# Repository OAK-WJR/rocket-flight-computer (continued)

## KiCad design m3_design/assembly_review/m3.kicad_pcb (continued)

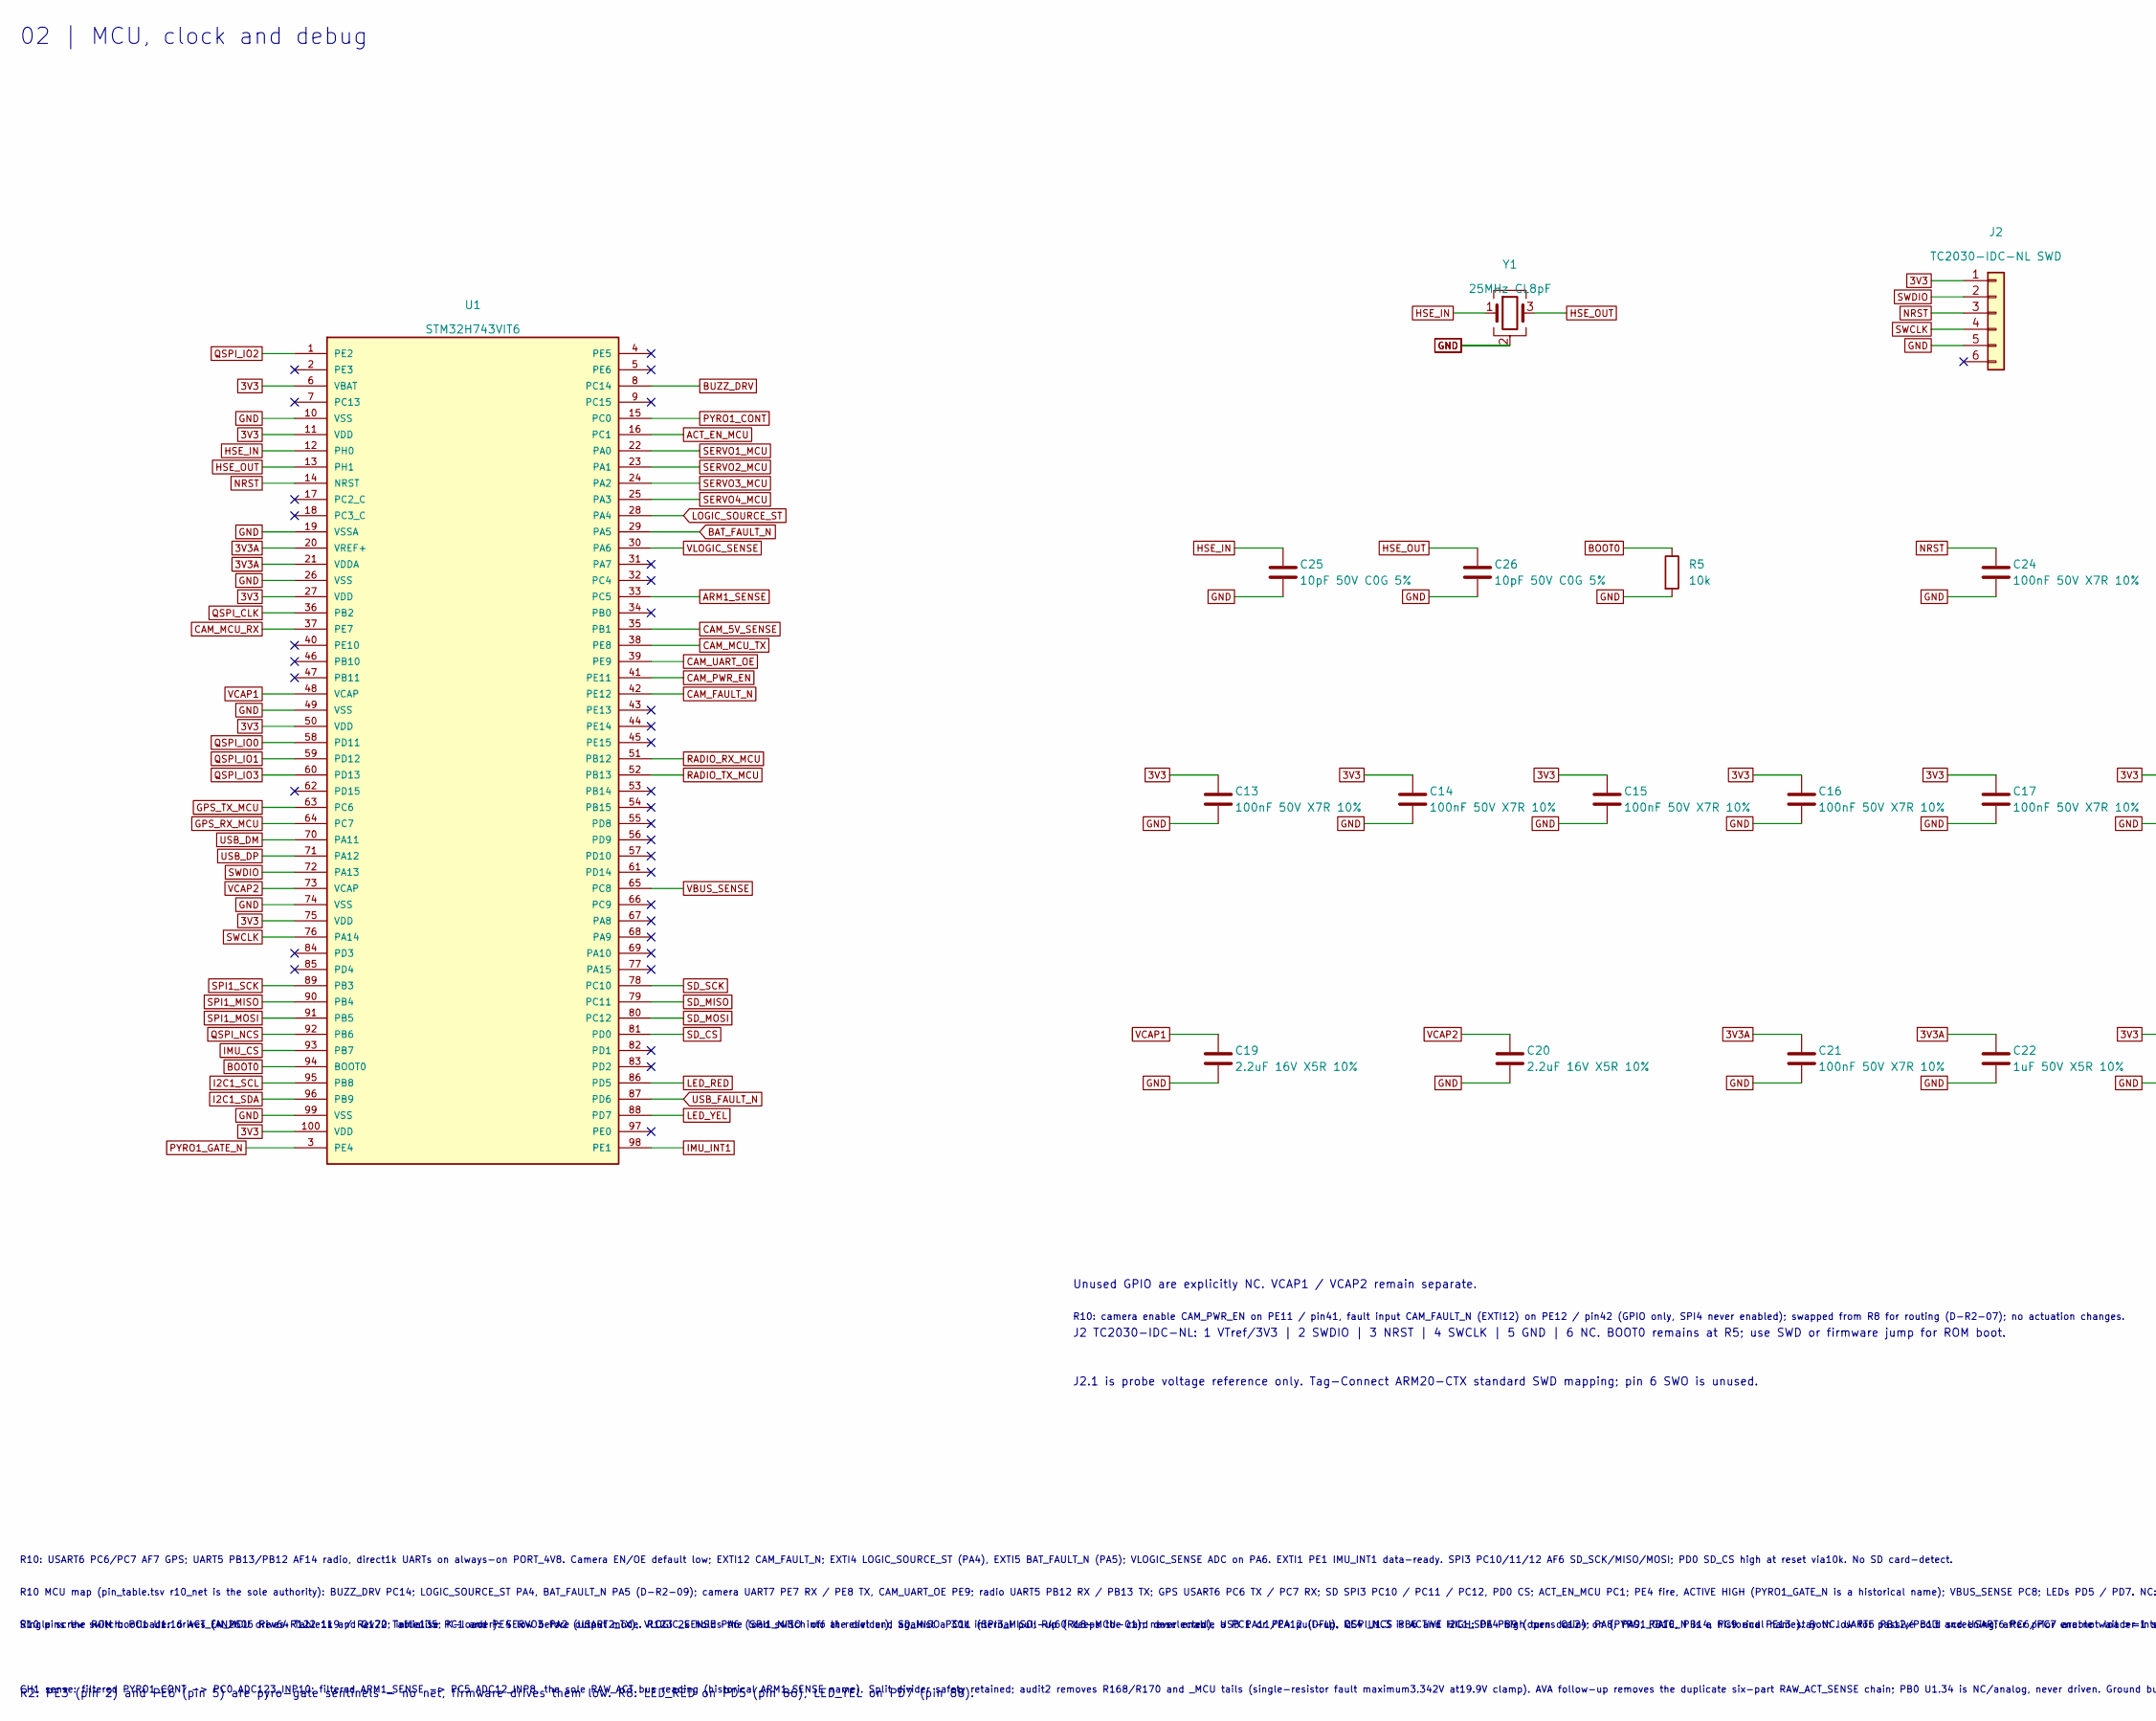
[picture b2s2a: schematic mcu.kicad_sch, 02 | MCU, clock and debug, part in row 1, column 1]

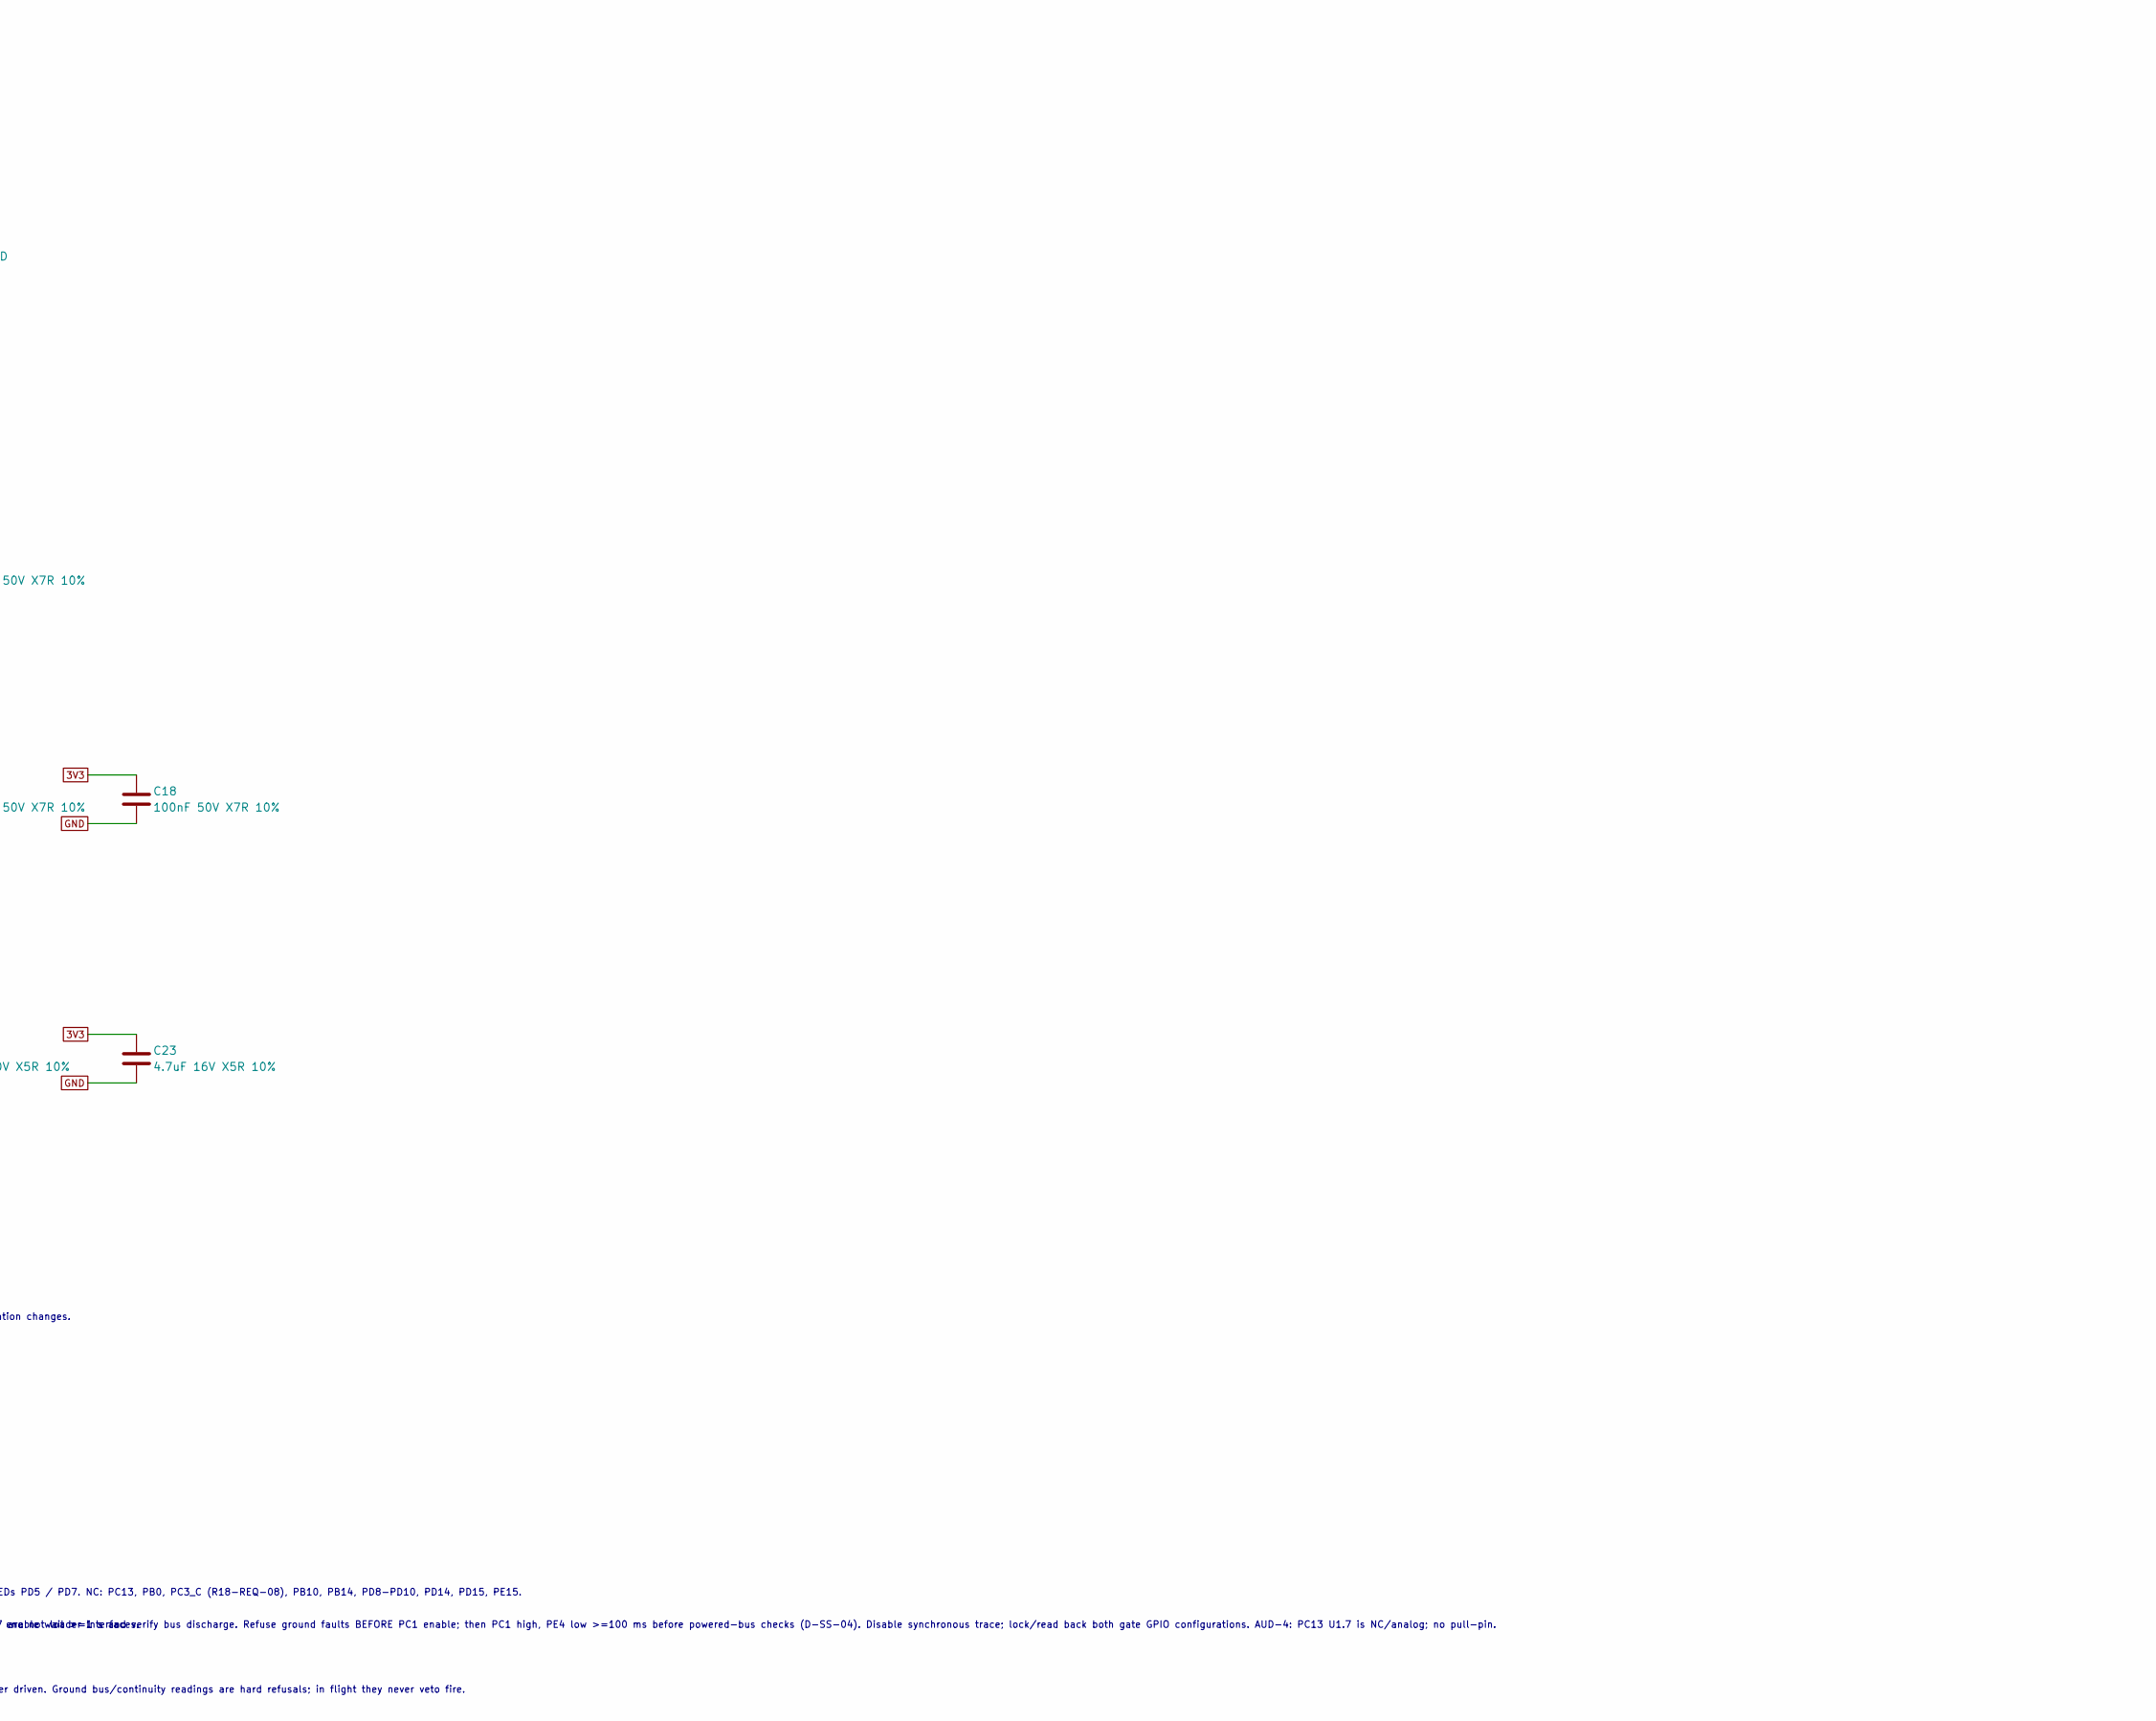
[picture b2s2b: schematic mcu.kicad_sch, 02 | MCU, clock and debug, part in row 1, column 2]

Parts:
C13, C14, C15, C16, C17, C18, C21, C24: 100nF 50V X7R 10%; C0402; Manufacturer Part CL05B104KB54PNC; LCSC C307331
C19, C20: 2.2uF 16V X5R 10%; C0603; Manufacturer Part CL10A225KO8NNNC; LCSC C23630
C22: 1uF 50V X5R 10%; C0603; Manufacturer Part CL10A105KB8NNNC; LCSC C15849
C23: 4.7uF 16V X5R 10%; C0603; Manufacturer Part CL10A475KO8NNNC; LCSC C19666
C25, C26: 10pF 50V C0G 5%; C0402; Manufacturer Part CL05C100JB5NNNC; LCSC C32949
J2: TC2030-IDC-NL SWD; M3_TC2030_IDC_NL; Manufacturer Part TC2030-IDC-NL
R5: 10k; R0402; Manufacturer Part 0402WGF1002TCE; LCSC C25744
U1: STM32H743VIT6; LQFP-100_L14.0-W14.0-P0.50-LS16.0-BL; Manufacturer Part STM32H743VIT6TR; LCSC C5271084
Y1: 25MHz CL8pF; CRYSTAL-SMD_4P-L3.2-W2.5-BL; Manufacturer Part NX3225GA-25.000M-STD-CRG-2; LCSC C1985619

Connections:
3V3: C13.1, C14.1, C15.1, C16.1, C17.1, C18.1, C23.1, J2.1, U1.6 (VBAT), U1.11 (VDD), U1.27 (VDD), U1.50 (VDD), U1.75 (VDD), U1.100 (VDD); also elsewhere on the board
3V3A: C21.1, C22.1, U1.20 (VREF+), U1.21 (VDDA); also elsewhere on the board
ACT_EN_MCU: U1.16 (PC1); also elsewhere on the board
ARM1_SENSE: U1.33 (PC5); also elsewhere on the board
BAT_FAULT_N: U1.29 (PA5); also elsewhere on the board
BOOT0: R5.1, U1.94 (BOOT0)
BUZZ_DRV: U1.8 (PC14); also elsewhere on the board
CAM_5V_SENSE: U1.35 (PB1); also elsewhere on the board
CAM_FAULT_N: U1.42 (PE12); also elsewhere on the board
CAM_MCU_RX: U1.37 (PE7); also elsewhere on the board
CAM_MCU_TX: U1.38 (PE8); also elsewhere on the board
CAM_PWR_EN: U1.41 (PE11); also elsewhere on the board
CAM_UART_OE: U1.39 (PE9); also elsewhere on the board
GND: C13.2, C14.2, C15.2, C16.2, C17.2, C18.2, C19.2, C20.2, C21.2, C22.2, C23.2, C24.2, C25.2, C26.2, J2.5, R5.2, U1.10 (VSS), U1.19 (VSSA), U1.26 (VSS), U1.49 (VSS), U1.74 (VSS), U1.99 (VSS), Y1.2 (G), Y1.4 (G); also elsewhere on the board
GPS_RX_MCU: U1.56 (PD9); also elsewhere on the board
GPS_TX_MCU: U1.55 (PD8); also elsewhere on the board
HSE_IN: C25.1, U1.12 (PH0), Y1.1
HSE_OUT: C26.1, U1.13 (PH1), Y1.3
I2C1_SCL: U1.95 (PB8); also elsewhere on the board
I2C1_SDA: U1.96 (PB9); also elsewhere on the board
IMU_CS: U1.93 (PB7); also elsewhere on the board
IMU_INT1: U1.98 (PE1); also elsewhere on the board
LED_RED: U1.86 (PD5); also elsewhere on the board
LED_YEL: U1.88 (PD7); also elsewhere on the board
LOGIC_SOURCE_ST: U1.28 (PA4); also elsewhere on the board
NRST: C24.1, J2.3, U1.14 (NRST)
PYRO1_CONT: U1.15 (PC0); also elsewhere on the board
PYRO1_GATE_N: U1.3 (PE4); also elsewhere on the board
QSPI_CLK: U1.36 (PB2); also elsewhere on the board
QSPI_IO0: U1.58 (PD11); also elsewhere on the board
QSPI_IO1: U1.59 (PD12); also elsewhere on the board
QSPI_IO2: U1.1 (PE2); also elsewhere on the board
QSPI_IO3: U1.60 (PD13); also elsewhere on the board
QSPI_NCS: U1.92 (PB6); also elsewhere on the board
RADIO_RX_MCU: U1.51 (PB12); also elsewhere on the board
RADIO_TX_MCU: U1.52 (PB13); also elsewhere on the board
SD_CS: U1.81 (PD0); also elsewhere on the board
SD_MISO: U1.79 (PC11); also elsewhere on the board
SD_MOSI: U1.80 (PC12); also elsewhere on the board
SD_SCK: U1.78 (PC10); also elsewhere on the board
SERVO1_MCU: U1.22 (PA0); also elsewhere on the board
SERVO2_MCU: U1.23 (PA1); also elsewhere on the board
SERVO3_MCU: U1.24 (PA2); also elsewhere on the board
SERVO4_MCU: U1.25 (PA3); also elsewhere on the board
SPI1_MISO: U1.90 (PB4); also elsewhere on the board
SPI1_MOSI: U1.91 (PB5); also elsewhere on the board
SPI1_SCK: U1.89 (PB3); also elsewhere on the board
SWCLK: J2.4, U1.76 (PA14)
SWDIO: J2.2, U1.72 (PA13)
USB_DM: U1.70 (PA11); also elsewhere on the board
USB_DP: U1.71 (PA12); also elsewhere on the board
USB_FAULT_N: U1.87 (PD6); also elsewhere on the board
VBUS_SENSE: U1.65 (PC8); also elsewhere on the board
VCAP1: C19.1, U1.48 (VCAP)
VCAP2: C20.1, U1.73 (VCAP)
VLOGIC_SENSE: U1.30 (PA6); also elsewhere on the board

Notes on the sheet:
02 | MCU, clock and debug
Unused GPIO are explicitly NC. VCAP1 / VCAP2 remain separate.
J2 TC2030-IDC-NL: 1 VTref/3V3 | 2 SWDIO | 3 NRST | 4 SWCLK | 5 GND | 6 NC. BOOT0 remains at R5; use SWD or firmware jump for ROM boot.
J2.1 is probe voltage reference only. Tag-Connect ARM20-CTX standard SWD mapping; pin 6 SWO is unused.
R2: PE3 (pin 2) and PE6 (pin 5) are pyro-gate sentinels - no net, firmware drives them low. R8: LED_RED on PD5 (pin 86), LED_YEL on PD7 (pin 88).
R10: USART6 PC6/PC7 AF7 GPS; UART5 PB13/PB12 AF14 radio, direct1k UARTs on always-on PORT_4V8. Camera EN/OE default low; EXTI12 CAM_FAULT_N; EXTI4 LOGIC_SOURCE_ST (PA4), EXTI5 BAT_FAULT_N (PA5); VLOGIC_SENSE ADC on PA6. EXTI1 PE1 IMU_INT1 data-ready. SPI3 PC10/11/12 AF6 SD_SCK/MISO/MOSI; PD0 SD_CS 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
Single screw switch: PC1 U1.16 ACT_EN_MCU drives R122 1k and Q122; initialise PC1 and PE4 low before output mode. R123 2k holds the load switch off at reset and against a 30k internal pull-up (R18-MCU-01); never enable a PC1 or PE4 pull-up. PE4 U1.3 is ACTIVE HIGH: PE4 high turns Q124 on (PYRO1_GAT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
R10: camera enable CAM_PWR_EN on PE11 / pin41, fault input CAM_FAULT_N (EXTI12) on PE12 / pin42 (GPIO only, SPI4 never enabled); swapped from R8 for routing (D-R2-07); no actuation changes.
R10 MCU map (pin_table.tsv r10_net is the sole authority): BUZZ_DRV PC14; LOGIC_SOURCE_ST PA4, BAT_FAULT_N PA5 (D-R2-09); camera UART7 PE7 RX / PE8 TX, CAM_UART_OE PE9; radio UART5 PB12 RX / PB13 TX; GPS USART6 PC6 TX / PC7 RX; SD SPI3 PC10 / PC11 / PC12, PD0 CS; ACT_EN_MCU PC1; PE4 fire, ACTIVE HI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
R10 pins the ROM bootloader drives (AN2606 Rev64 Table119 / Rev70 Table135; K-loader): SERVO3 PA2 (USART2_TX), VLOGIC_SENSE PA6 (SPI1_MISO into the divider), SD_MISO PC11 (SPI3_MISO; R460 keeps the card deselected), USB PA11/PA12 (DFU), QSPI_NCS PB6 and I2C1_SDA PB9 (open drain); PA8, PA9, PB10, PB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
CH1 sense: filtered PYRO1_CONT -> PC0 ADC123_INP10; filtered ARM1_SENSE -> PC5 ADC12_INP8, the sole RAW_ACT bus reading (historical ARM1_SENSE name). Split divider safety retained; audit2 removes R168/R170 and _MCU tails (single-resistor fault maximum3.342V at19.9V clamp). AVA follow-up removes the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

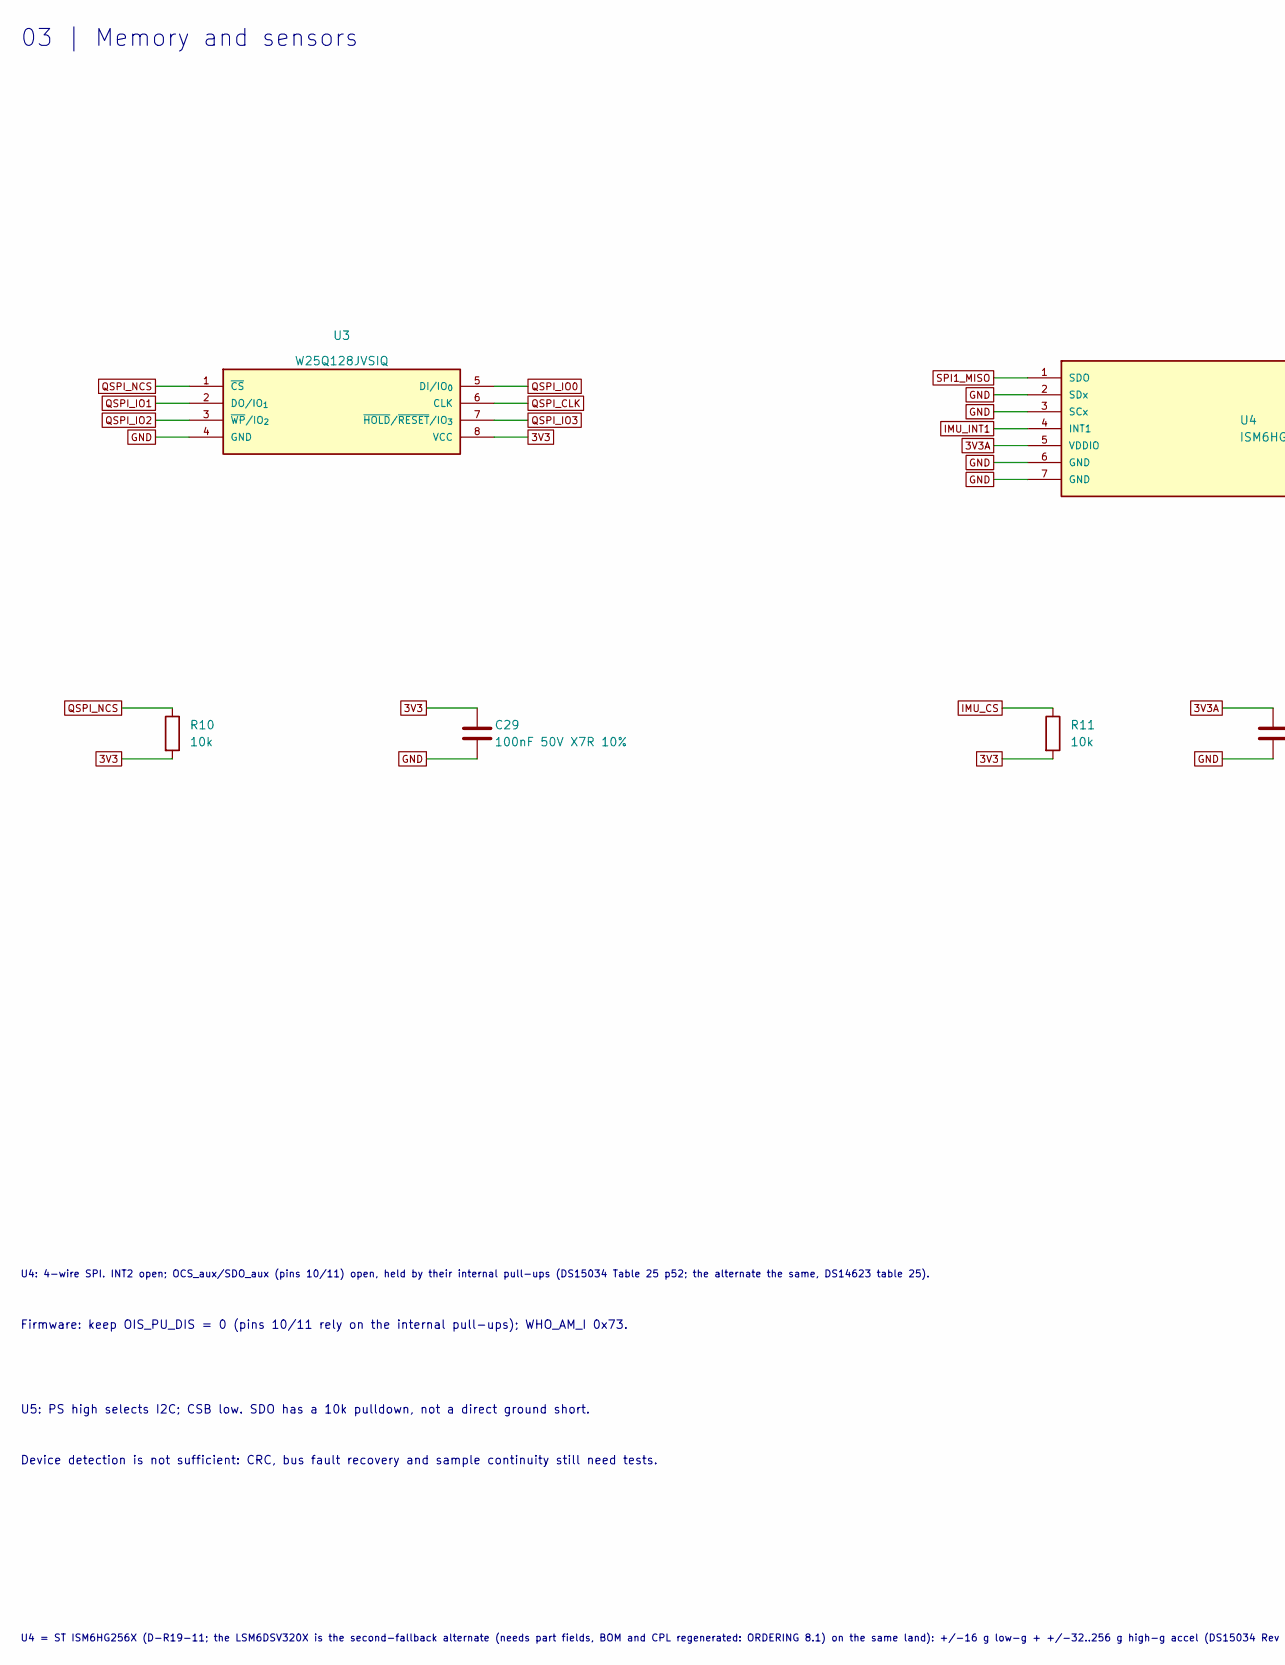
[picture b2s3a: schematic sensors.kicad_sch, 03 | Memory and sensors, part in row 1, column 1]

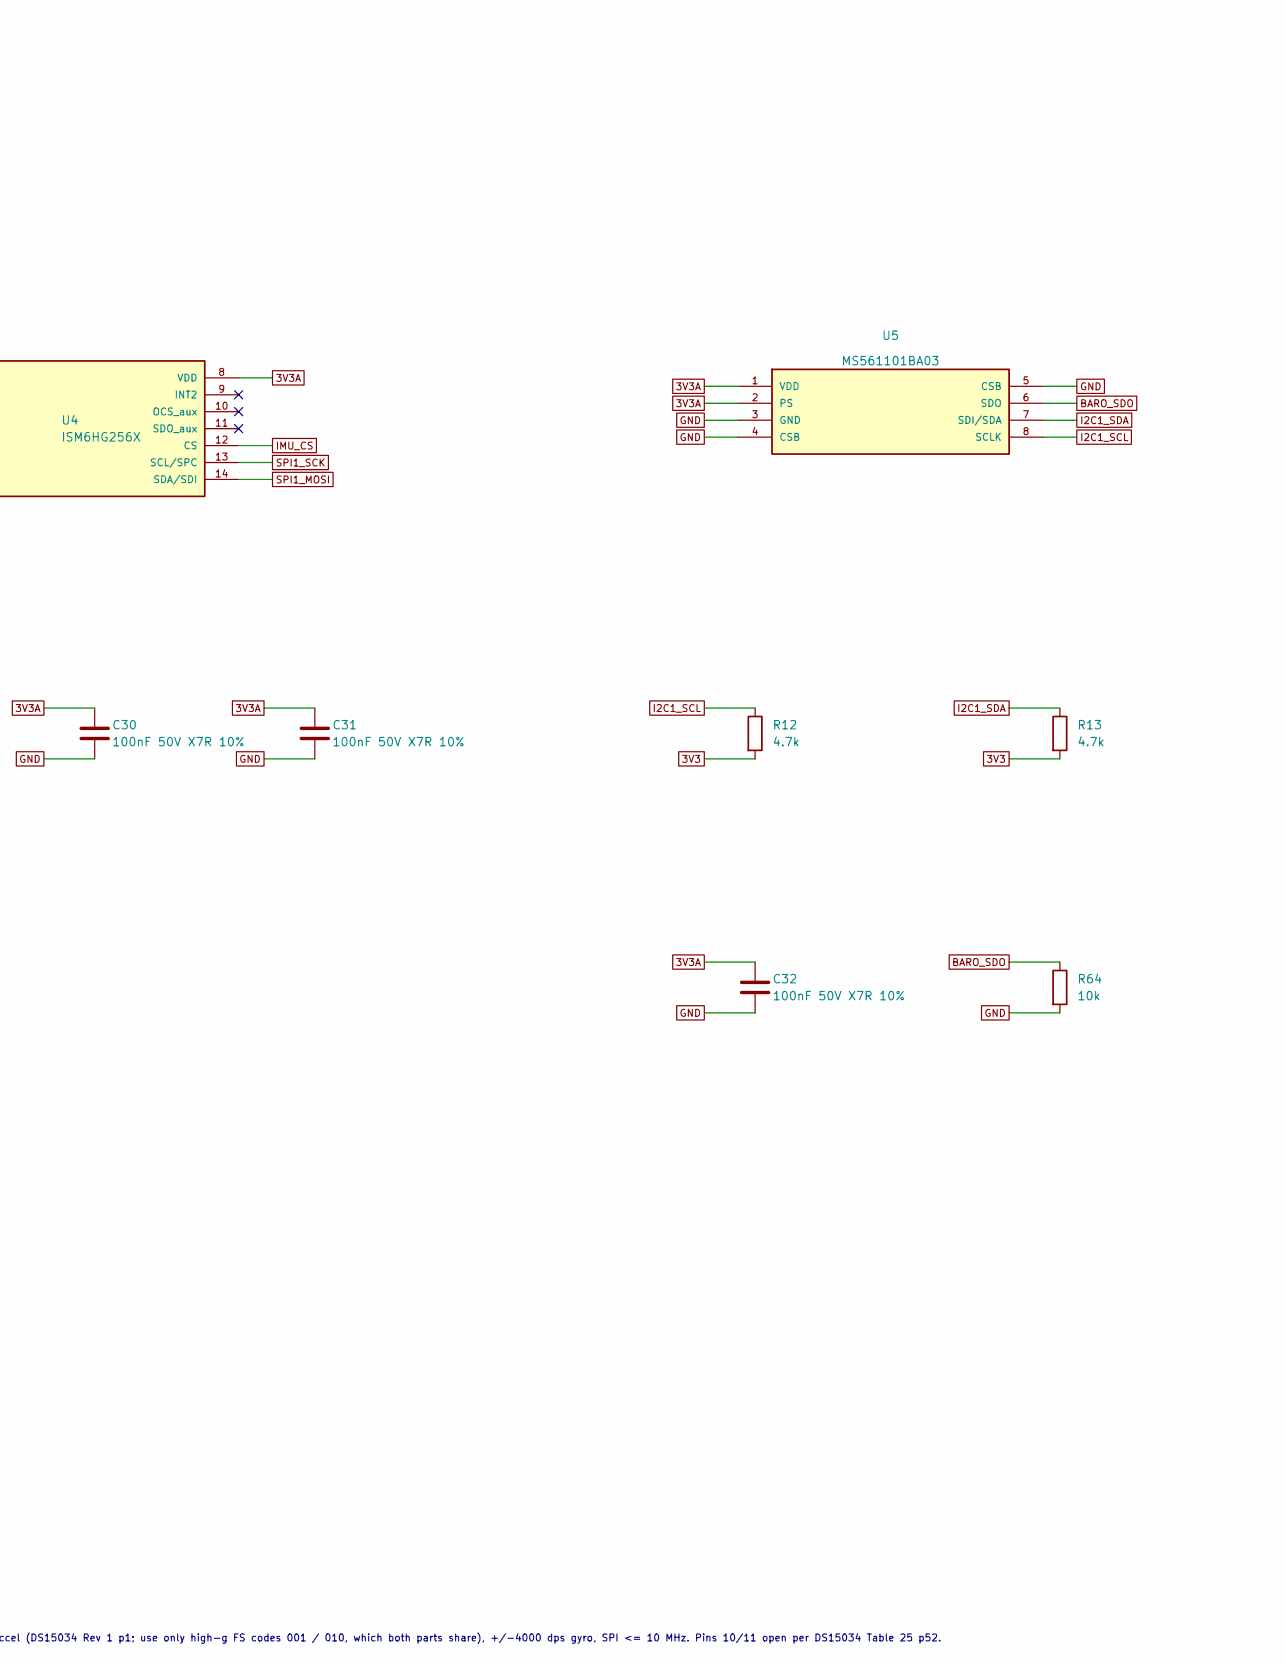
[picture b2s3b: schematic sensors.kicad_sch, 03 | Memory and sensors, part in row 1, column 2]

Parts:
C29, C30, C31, C32: 100nF 50V X7R 10%; C0402; Manufacturer Part CL05B104KB54PNC; LCSC C307331
R10, R11, R64: 10k; R0402; Manufacturer Part 0402WGF1002TCE; LCSC C25744
R12, R13: 4.7k; R0402; Manufacturer Part 0402WGF4701TCE; LCSC C25900
U3: W25Q128JVSIQ; SOIC-8_L5.3-W5.3-P1.27-LS8.0-BL; Manufacturer Part W25Q128JVSIQ; LCSC C97521
U4: ISM6HG256X; LGA-14_L3.0-W2.5-P0.50-TL; Manufacturer Part ISM6HG256XTR; LCSC C51931514
U5: MS561101BA03; SENSORS-SMD_MS5611-01BA03; Manufacturer Part MS561101BA03-50; LCSC C15639

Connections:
3V3: C29.1, R10.2, R11.2, R12.2, R13.2, U3.8 (VCC); also elsewhere on the board
3V3A: C30.1, C31.1, C32.1, U4.5 (VDDIO), U4.8 (VDD), U5.1 (VDD), U5.2 (PS); also elsewhere on the board
BARO_SDO: R64.1, U5.6 (SDO)
GND: C29.2, C30.2, C31.2, C32.2, R64.2, U3.4 (GND), U4.2 (SDx), U4.3 (SCx), U4.6 (GND), U4.7 (GND), U5.3 (GND), U5.4 (CSB), U5.5 (CSB); also elsewhere on the board
I2C1_SCL: R12.1, U5.8 (SCLK); also elsewhere on the board
I2C1_SDA: R13.1, U5.7 (SDI/SDA); also elsewhere on the board
IMU_CS: R11.1, U4.12 (CS); also elsewhere on the board
IMU_INT1: U4.4 (INT1); also elsewhere on the board
QSPI_CLK: U3.6 (CLK); also elsewhere on the board
QSPI_IO0: U3.5 (DI/IO_{0}); also elsewhere on the board
QSPI_IO1: U3.2 (DO/IO_{1}); also elsewhere on the board
QSPI_IO2: U3.3 (~WP/IO_{2}); also elsewhere on the board
QSPI_IO3: U3.7 (~HOLD/~RESET/IO_{3}); also elsewhere on the board
QSPI_NCS: R10.1, U3.1 (~CS); also elsewhere on the board
SPI1_MISO: U4.1 (SDO); also elsewhere on the board
SPI1_MOSI: U4.14 (SDA/SDI); also elsewhere on the board
SPI1_SCK: U4.13 (SCL/SPC); also elsewhere on the board

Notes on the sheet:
03 | Memory and sensors
Firmware: keep OIS_PU_DIS = 0 (pins 10/11 rely on the internal pull-ups); WHO_AM_I 0x73.
U5: PS high selects I2C; CSB low. SDO has a 10k pulldown, not a direct ground short.
Device detection is not sufficient: CRC, bus fault recovery and sample continuity still need tests.
U4 = ST ISM6HG256X (D-R19-11; the LSM6DSV320X is the second-fallback alternate (needs part fields, BOM and CPL regenerated: ORDERING 8.1) on the same land): +/-16 g low-g + +/-32..256 g high-g accel (DS15034 Rev 1 p1; use only high-g FS codes 001 / 010, which both parts share), +/-4000 dps gyro, SP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
U4: 4-wire SPI. INT2 open; OCS_aux/SDO_aux (pins 10/11) open, held by their internal pull-ups (DS15034 Table 25 p52; the alternate the same, DS14623 table 25).

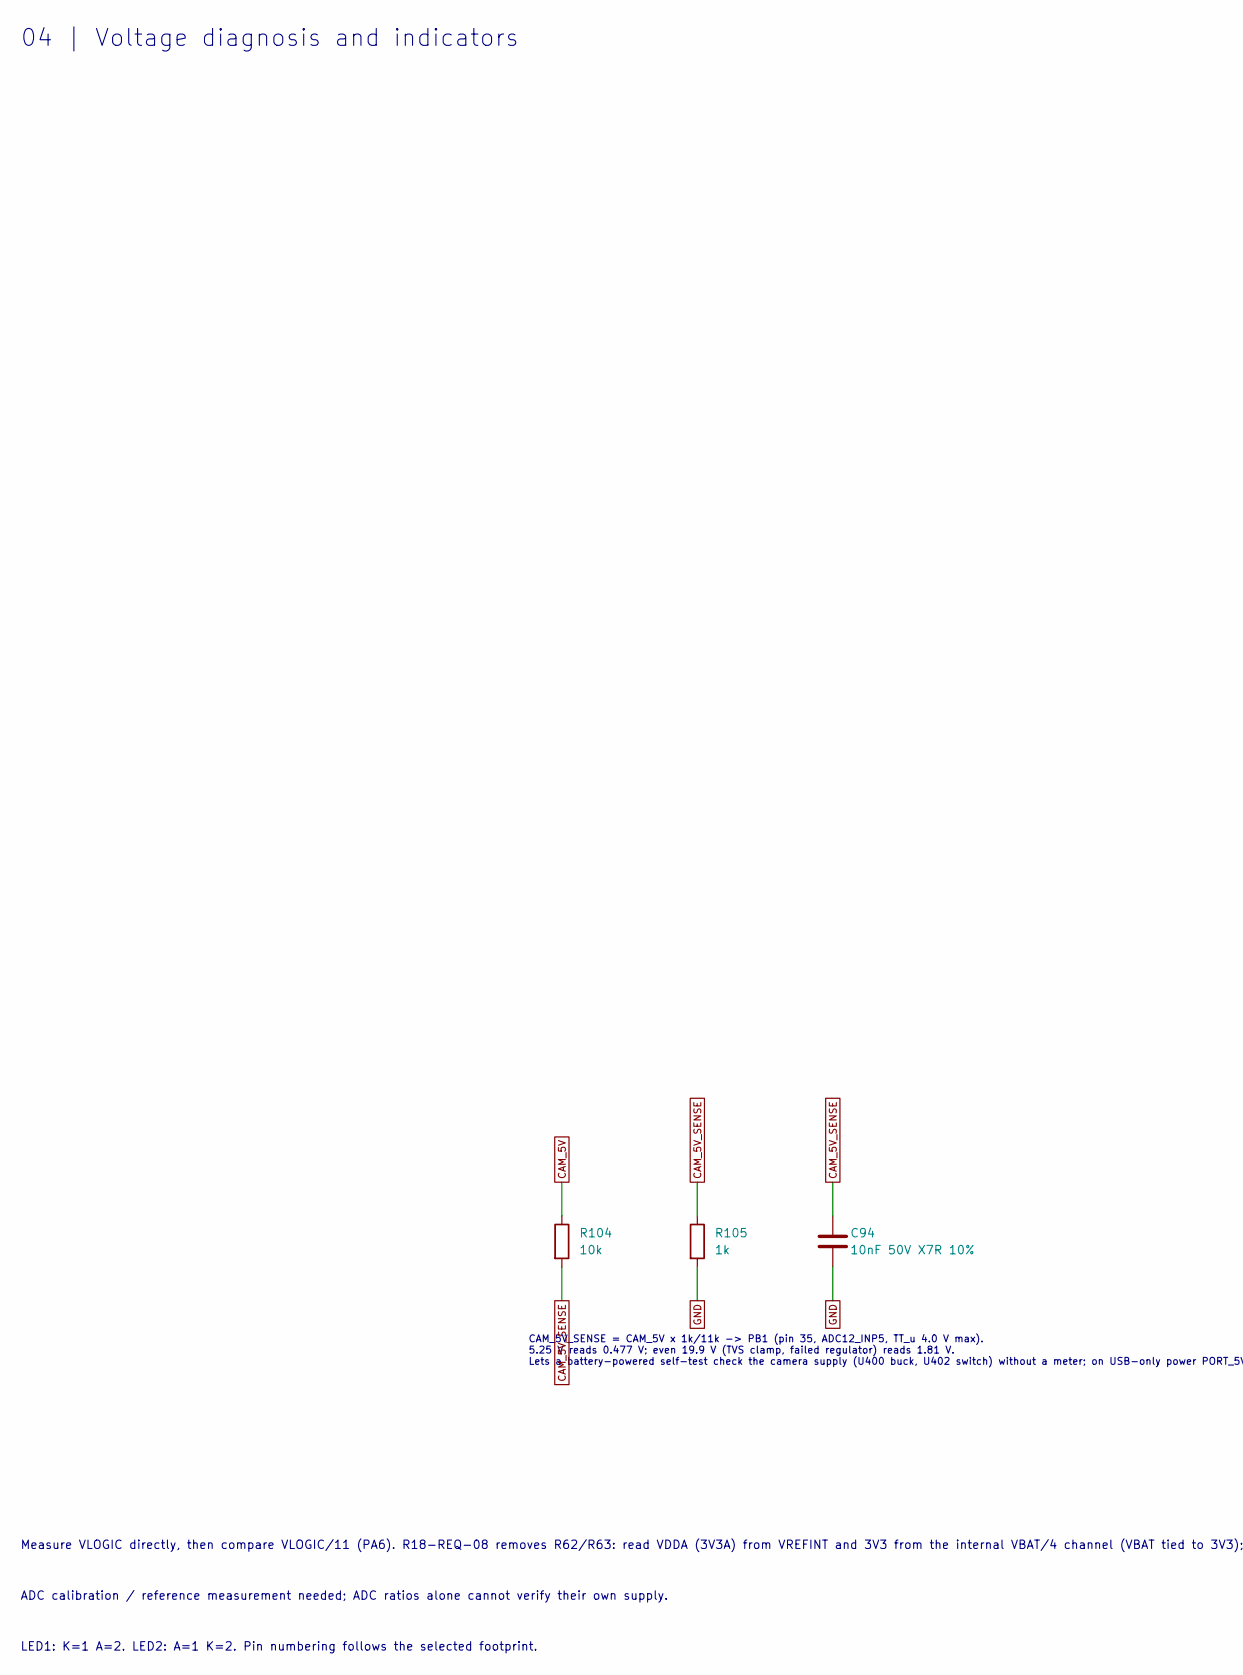
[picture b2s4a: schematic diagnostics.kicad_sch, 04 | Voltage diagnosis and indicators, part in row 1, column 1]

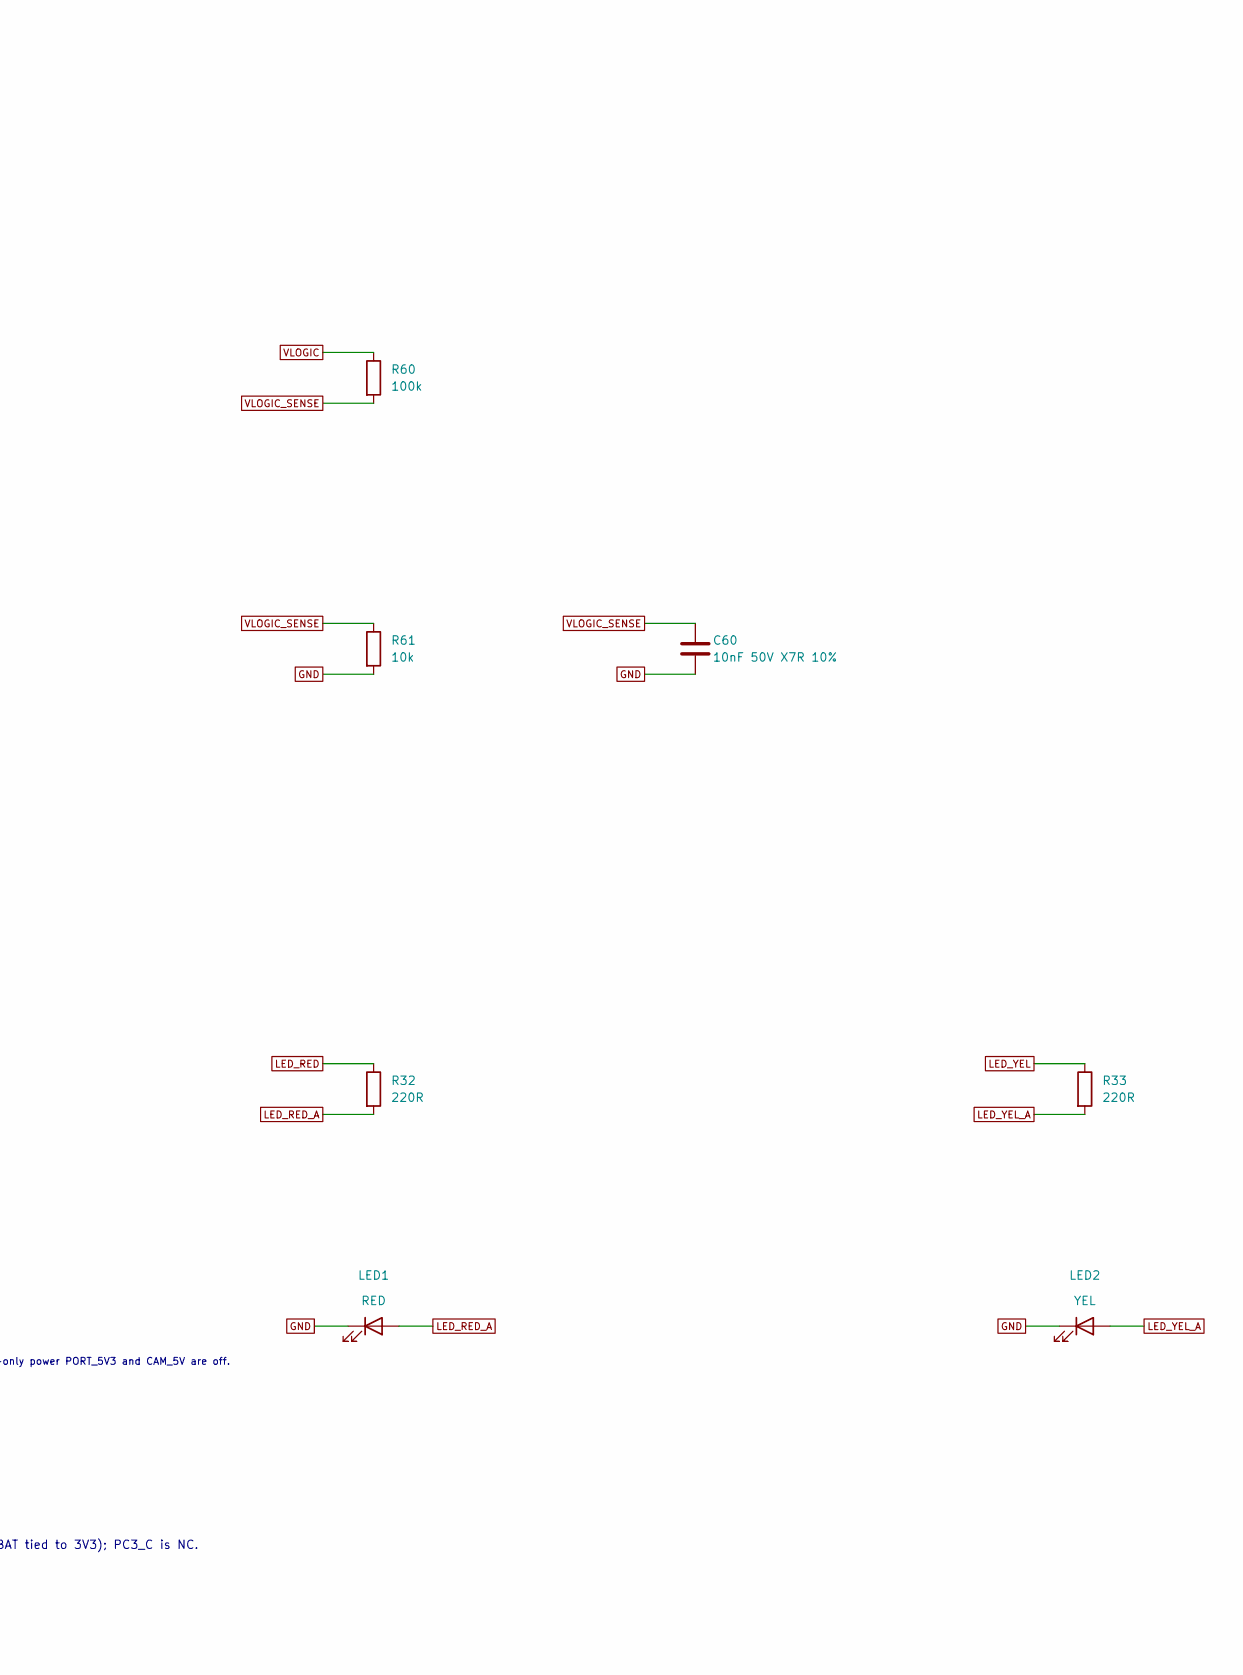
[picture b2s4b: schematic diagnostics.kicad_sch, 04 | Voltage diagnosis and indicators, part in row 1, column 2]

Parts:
C60, C94: 10nF 50V X7R 10%; C0603; Manufacturer Part 0603B103K500NT; LCSC C57112
LED1: RED; M3_NCD0805R1_K1; Manufacturer Part NCD0805R1; LCSC C84256
LED2: YEL; M3_KT0805Y_A1; Manufacturer Part KT-0805Y; LCSC C2296
R32, R33: 220R; R0805; Manufacturer Part 0805W8F2200T5E; LCSC C17557
R60: 100k; R0402; Manufacturer Part 0402WGF1003TCE; LCSC C25741
R61, R104: 10k; R0402; Manufacturer Part 0402WGF1002TCE; LCSC C25744
R105: 1k; R0402; Manufacturer Part 0402WGF1001TCE; LCSC C11702

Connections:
CAM_5V: R104.1; also elsewhere on the board
CAM_5V_SENSE: C94.1, R104.2, R105.1; also elsewhere on the board
GND: C60.2, C94.2, LED1.1 (K), LED2.2 (K), R61.2, R105.2; also elsewhere on the board
LED_RED: R32.1; also elsewhere on the board
LED_RED_A: LED1.2 (A), R32.2
LED_YEL: R33.1; also elsewhere on the board
LED_YEL_A: LED2.1 (A), R33.2
VLOGIC: R60.1; also elsewhere on the board
VLOGIC_SENSE: C60.1, R60.2, R61.1; also elsewhere on the board

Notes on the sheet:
04 | Voltage diagnosis and indicators
Measure VLOGIC directly, then compare VLOGIC/11 (PA6). R18-REQ-08 removes R62/R63: read VDDA (3V3A) from VREFINT and 3V3 from the internal VBAT/4 channel (VBAT tied to 3V3); PC3_C is NC.
ADC calibration / reference measurement needed; ADC ratios alone cannot verify their own supply.
LED1: K=1 A=2. LED2: A=1 K=2. Pin numbering follows the selected footprint.
CAM_5V_SENSE = CAM_5V x 1k/11k -> PB1 (pin 35, ADC12_INP5, TT_u 4.0 V max). 5.25 V reads 0.477 V; even 19.9 V (TVS clamp, failed regulator) reads 1.81 V. Lets a battery-powered self-test check the camera supply (U400 buck, U402 switch) without a meter; on USB-only power PORT_5V3 and CAM_5V are off.
